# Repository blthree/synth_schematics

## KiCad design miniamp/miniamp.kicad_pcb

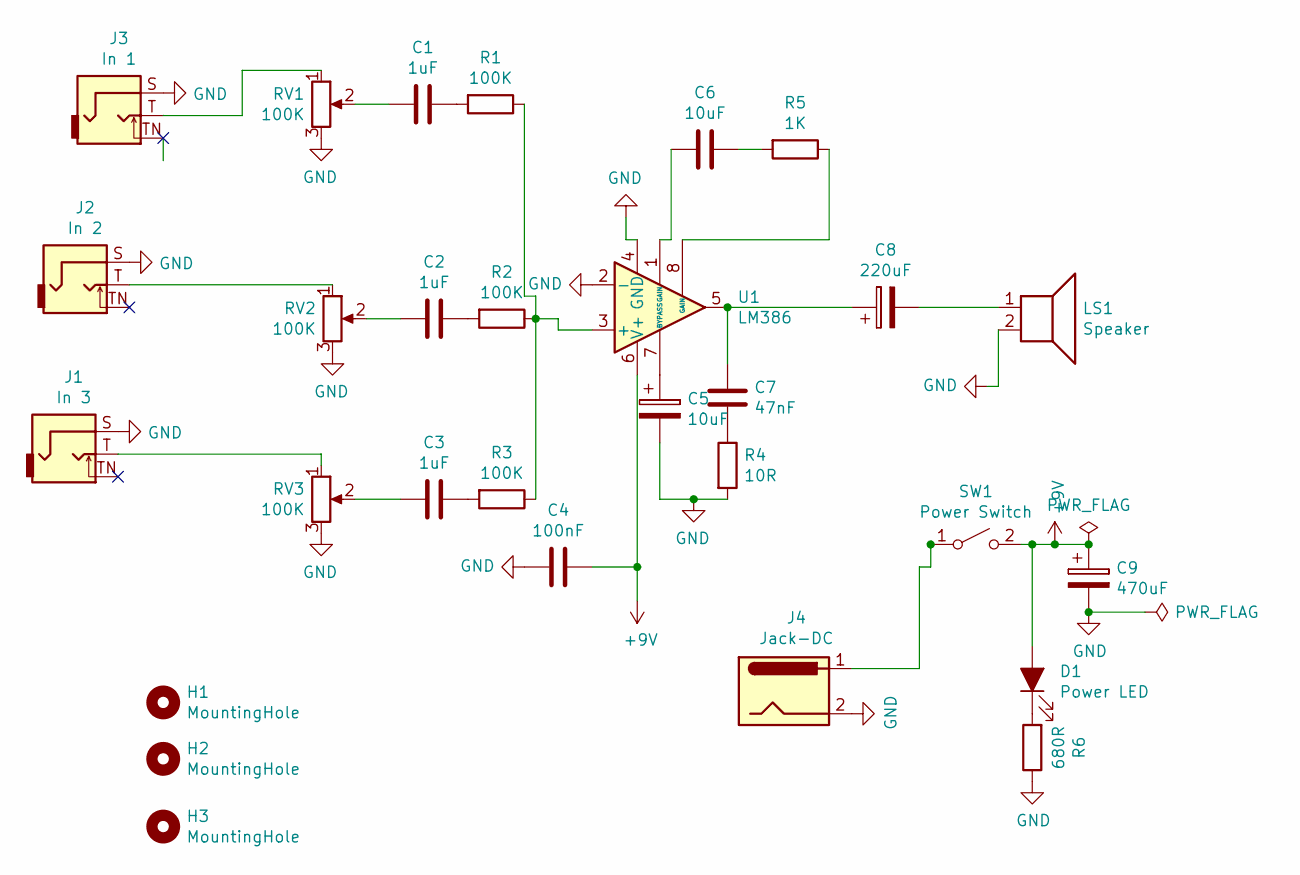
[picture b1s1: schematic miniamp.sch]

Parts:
C1, C2, C3: 1uF; C_Disc_D5.0mm_W2.5mm_P5.00mm
C4: 100nF; C_Disc_D5.0mm_W2.5mm_P5.00mm
C5: 10uF; CP_Radial_D5.0mm_P2.50mm
C6: 10uF; C_Disc_D5.0mm_W2.5mm_P5.00mm
C7: 47nF; C_Disc_D5.0mm_W2.5mm_P5.00mm
C8: 220uF; CP_Radial_D6.3mm_P2.50mm
C9: 470uF; CP_Radial_D6.3mm_P2.50mm
D1: Power LED; LED_D5.0mm
H1, H2, H3: MountingHole; MountingHole_3.2mm_M3_ISO7380
J1: In 3; CUI_SJ2-3592B-SMT-TR
J2: In 2; CUI_SJ2-3592B-SMT-TR
J3: In 1; CUI_SJ2-3592B-SMT-TR
J4: Jack-DC; BarrelJack_CUI_PJ-102AH_Horizontal
LS1: Speaker; JST_PH_B2B-PH-K_1x02_P2.00mm_Vertical
R1, R2, R3: 100K; R_Axial_DIN0207_L6.3mm_D2.5mm_P5.08mm_Vertical
R4: 10R; R_Axial_DIN0207_L6.3mm_D2.5mm_P5.08mm_Vertical
R5: 1K; R_Axial_DIN0207_L6.3mm_D2.5mm_P5.08mm_Vertical
R6: 680R; R_Axial_DIN0207_L6.3mm_D2.5mm_P5.08mm_Vertical
RV1, RV2, RV3: 100K; Potentiometer_Bourns_PTV09A-1_Single_Vertical
SW1: Power Switch; JST_PH_B2B-PH-K_1x02_P2.00mm_Vertical
U1: LM386; DIP-8_W7.62mm_Socket

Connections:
+9V: C4.1, C9.1, D1.2 (A), SW1.2 (B), U1.6 (V+)
GND: C4.2, C5.2, C9.2, J1.S, J2.S, J3.S, J4.2, LS1.2, R4.2, R6.1, RV1.3, RV2.3, RV3.3, U1.2 (-), U1.4 (GND)
unnamed: C1.1, R1.2
unnamed: C1.2, RV1.2
unnamed: C2.1, R2.2
unnamed: C2.2, RV2.2
unnamed: C3.1, R3.2
unnamed: C3.2, RV3.2
unnamed: C5.1, U1.7 (BYPASS)
unnamed: C6.1, R5.2
unnamed: C6.2, U1.1 (GAIN)
unnamed: C7.1, C8.1, U1.5
unnamed: C7.2, R4.1
unnamed: C8.2, LS1.1
unnamed: D1.1 (K), R6.2
unnamed: J1.T, RV3.1
unnamed: J2.T, RV2.1
unnamed: J3.T, RV1.1
unnamed: J4.1, SW1.1 (A)
unnamed: R1.1, R2.1, R3.1, U1.3 (+)
unnamed: R5.1, U1.8 (GAIN)

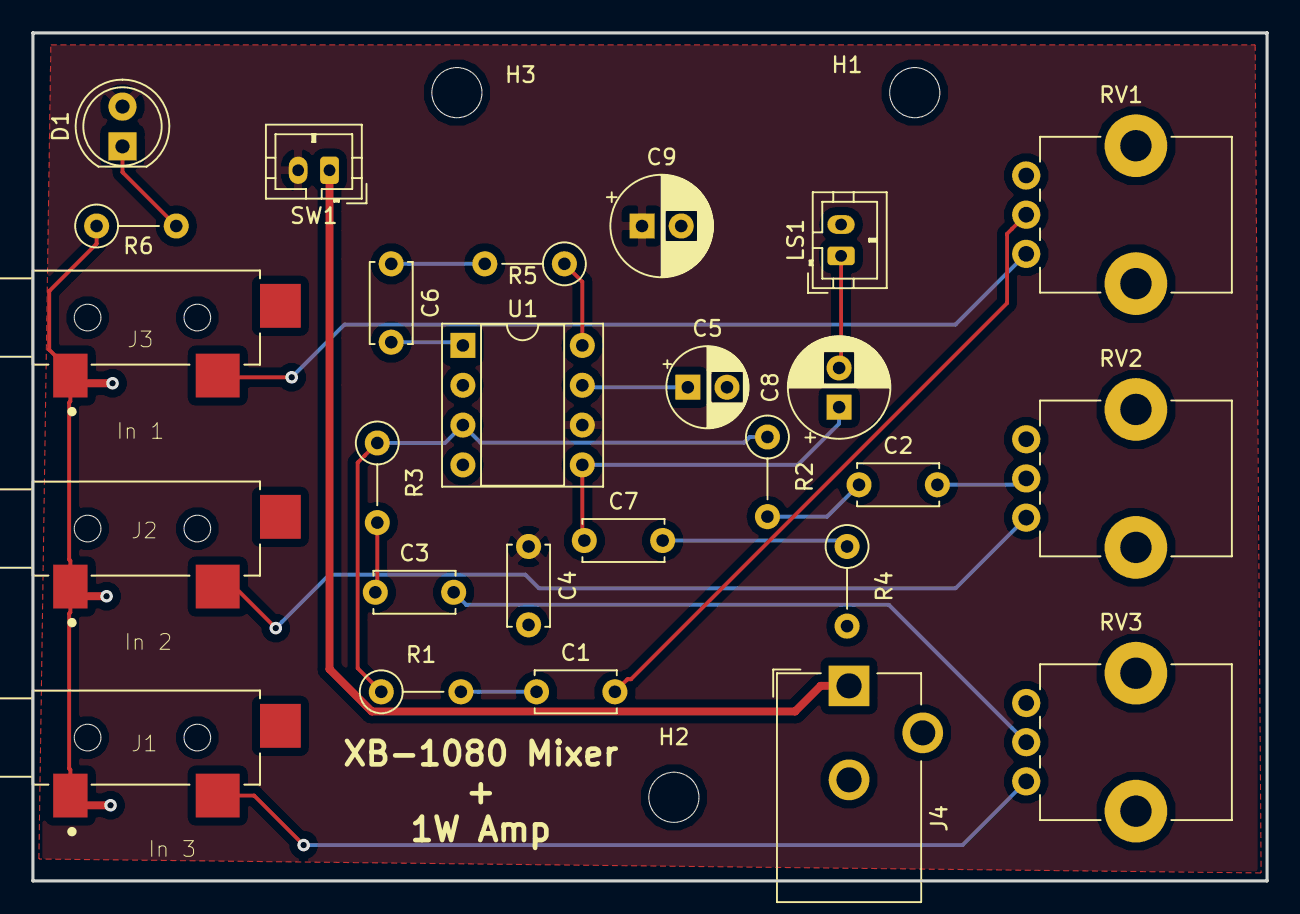
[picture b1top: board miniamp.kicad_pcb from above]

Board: 2 copper layers, 78.7 x 54.1 mm, 29 parts (0 on the bottom side), 21 nets.

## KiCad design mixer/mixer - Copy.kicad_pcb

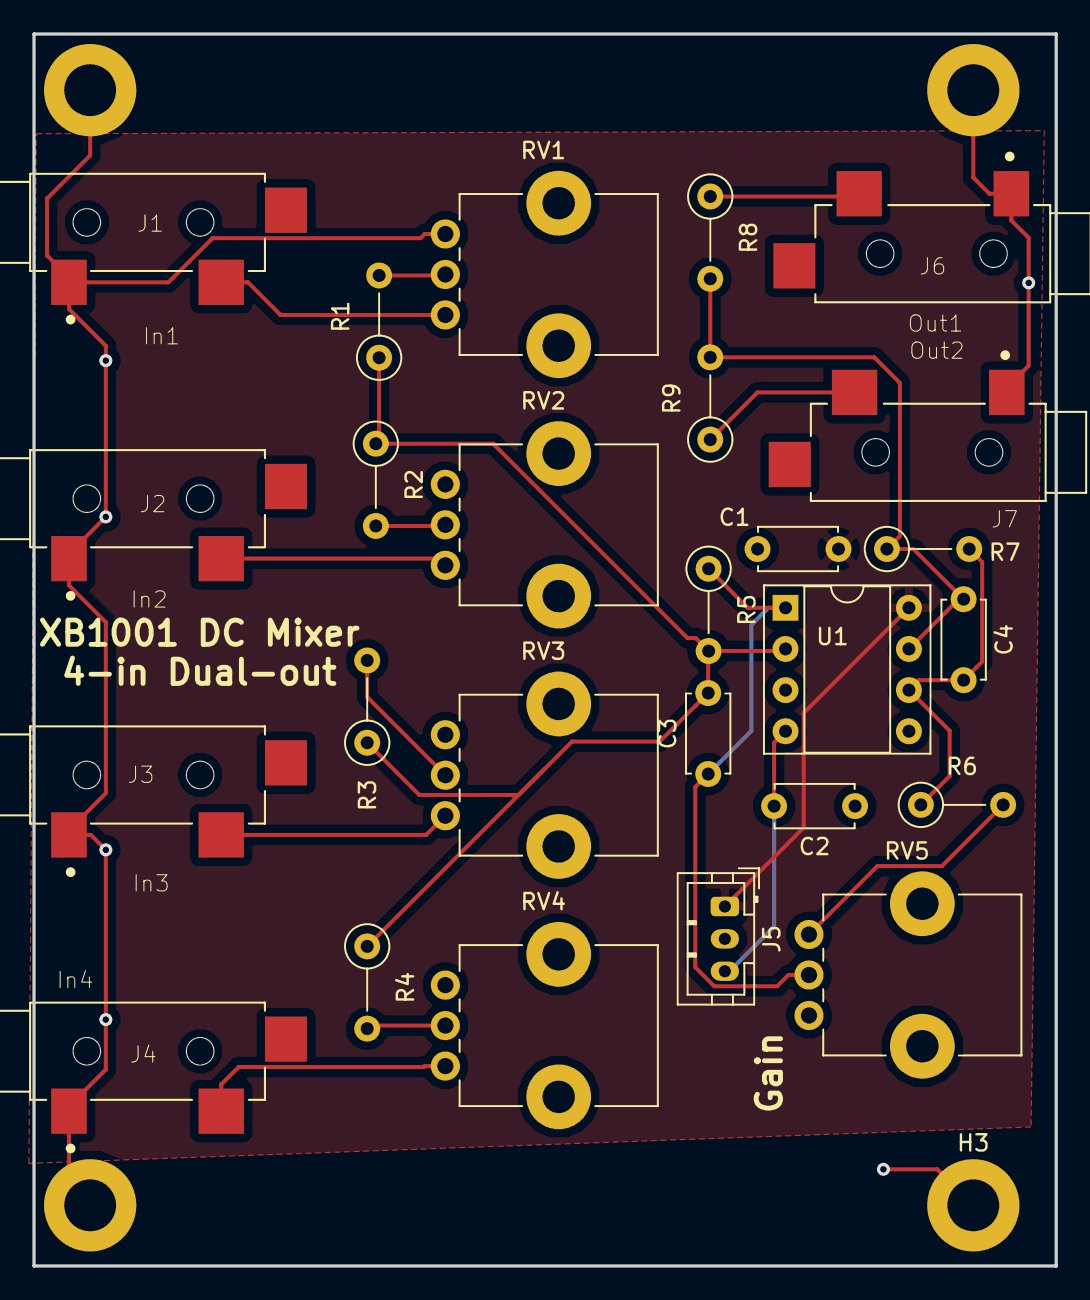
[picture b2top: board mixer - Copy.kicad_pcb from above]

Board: 2 copper layers, 63.1 x 76.1 mm, 30 parts (0 on the bottom side), 18 nets.

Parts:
C1, C2: 100nF; C_Disc_D4.7mm_W2.5mm_P5.00mm
C3, C4: 47pF; C_Disc_D4.7mm_W2.5mm_P5.00mm
H1, H2, H3, H4: MountingHole_Pad; MountingHole_3.2mm_M3_ISO7380_Pad
J1: In1; CUI_SJ2-3592B-SMT-TR
J2: In2; CUI_SJ2-3592B-SMT-TR
J3: In3; CUI_SJ2-3592B-SMT-TR
J4: In4; CUI_SJ2-3592B-SMT-TR
J5: Power; JST_PH_B3B-PH-K_1x03_P2.00mm_Vertical
J6: Out1; CUI_SJ2-3592B-SMT-TR
J7: Out2; CUI_SJ2-3592B-SMT-TR
R1, R2, R3, R4, R5, R7: 100K; R_Axial_DIN0207_L6.3mm_D2.5mm_P5.08mm_Vertical
R6: 10K; R_Axial_DIN0207_L6.3mm_D2.5mm_P5.08mm_Vertical
R8, R9: 1K; R_Axial_DIN0207_L6.3mm_D2.5mm_P5.08mm_Vertical
RV1, RV2, RV3, RV4, RV5: 104B; Potentiometer_Bourns_PTV09A-1_Single_Vertical
U1: TL072; DIP-8_W7.62mm_Socket

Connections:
+12V: C1.2, J5.1, U1.8
-12V: C2.2, J5.3, U1.4
GND: C1.1, C2.1, H1.1, H2.1, H3.1, H4.1, J1.S, J2.S, J3.S, J4.S, J5.2, J6.S, J7.S, RV1.3, RV2.3, RV3.3, RV4.3, U1.3, U1.5
unnamed: C3.1, R5.1, RV5.2, U1.1
unnamed: C3.2, R1.1, R2.1, R3.1, R4.1, R5.2, U1.2
unnamed: C4.1, R7.1, R8.2, R9.2, U1.7
unnamed: C4.2, R6.1, R7.2, U1.6
unnamed: J1.T, RV1.1
unnamed: J2.T, RV2.1
unnamed: J3.T, RV3.1
unnamed: J4.T, RV4.1
unnamed: J6.T, R8.1
unnamed: J7.T, R9.1
unnamed: R1.2, RV1.2
unnamed: R2.2, RV2.2
unnamed: R3.2, RV3.2
unnamed: R4.2, RV4.2
unnamed: R6.2, RV5.3

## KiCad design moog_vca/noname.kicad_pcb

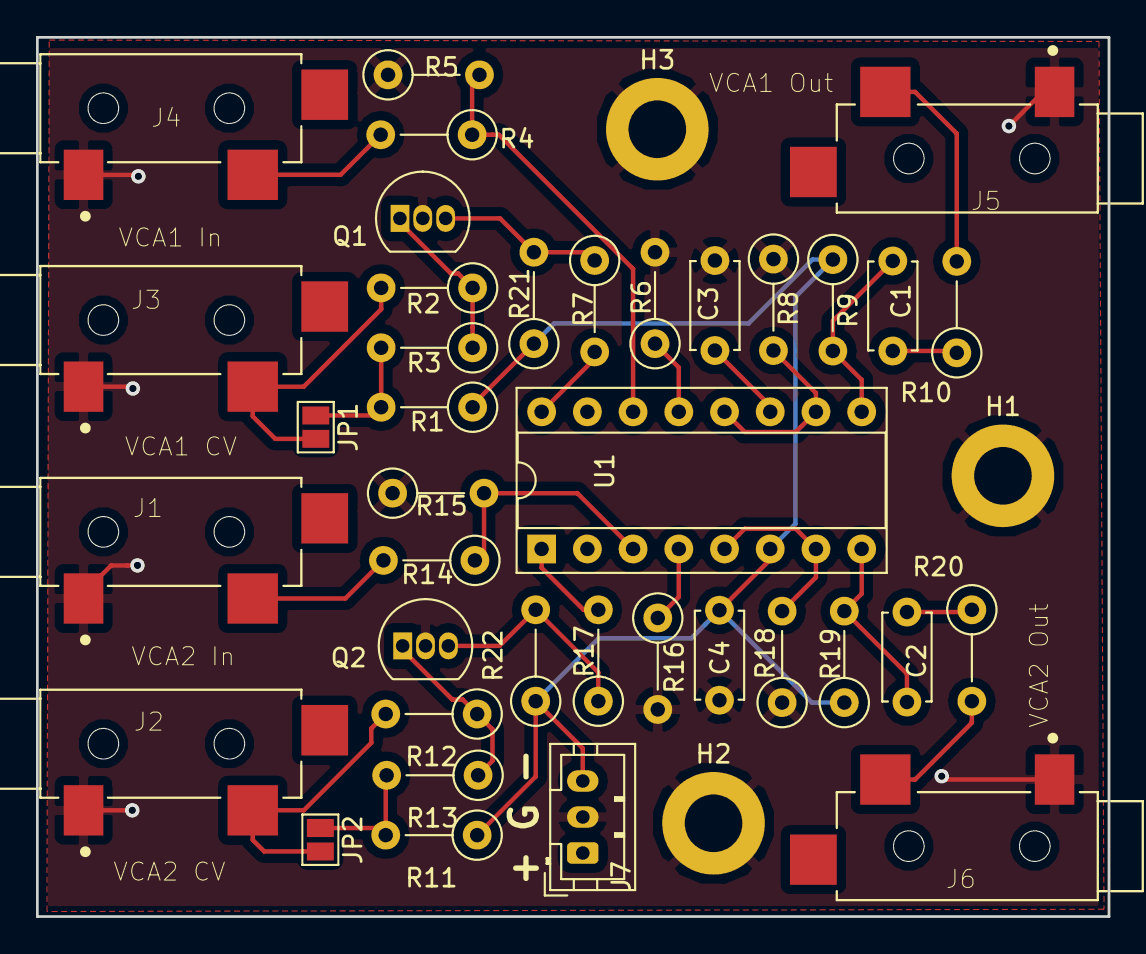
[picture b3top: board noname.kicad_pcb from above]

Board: 2 copper layers, 59.5 x 48.8 mm, 41 parts (0 on the bottom side), 27 nets.

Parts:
C1, C2: 2.2uF; C_Disc_D4.7mm_W2.5mm_P5.00mm
C3, C4: 0.10uF; C_Disc_D4.7mm_W2.5mm_P5.00mm
H1, H2, H3: MountingHole_Pad; MountingHole_3.2mm_M3_ISO7380_Pad
J1: VCA2 In; CUI_SJ2-3592B-SMT-TR
J2: VCA2 CV; CUI_SJ2-3592B-SMT-TR
J3: VCA1 CV; CUI_SJ2-3592B-SMT-TR
J4: VCA1 In; CUI_SJ2-3592B-SMT-TR
J5: VCA1 Out; CUI_SJ2-3592B-SMT-TR
J6: VCA2 Out; CUI_SJ2-3592B-SMT-TR
J7: Power; JST_PH_B3B-PH-K_1x03_P2.00mm_Vertical
JP1, JP2: Jumper_NO_Small; SolderJumper-2_P1.3mm_Open_Pad1.0x1.5mm
Q1, Q2: 2N3906; TO-92_Inline
R1, R11: 499k; R_Axial_DIN0207_L6.3mm_D2.5mm_P5.08mm_Vertical
R2, R3, R7, R12, R13, R17: 10k; R_Axial_DIN0207_L6.3mm_D2.5mm_P5.08mm_Vertical
R4, R14: 33.2k; R_Axial_DIN0207_L6.3mm_D2.5mm_P5.08mm_Vertical
R5, R6, R15, R16: 681R; R_Axial_DIN0207_L6.3mm_D2.5mm_P5.08mm_Vertical
R8, R18: 4.99k; R_Axial_DIN0207_L6.3mm_D2.5mm_P5.08mm_Vertical
R9, R19: 12,1k; R_Axial_DIN0207_L6.3mm_D2.5mm_P5.08mm_Vertical
R10, R20: 475R; R_Axial_DIN0207_L6.3mm_D2.5mm_P5.08mm_Vertical
R21, R22: 4.75M; R_Axial_DIN0207_L6.3mm_D2.5mm_P5.08mm_Vertical
U1: LM13700; DIP-16_W7.62mm_Socket

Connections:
+9V: C3.1, J7.1, U1.11
-9V: C4.1, J7.3, R1.1, R9.1, R11.1, R19.1, R21.1, R22.1, U1.6
GND: C3.2, C4.2, H1.1, H2.1, H3.1, J1.S, J2.S, J3.S, J4.S, J5.S, J6.S, J7.2, Q1.2, Q2.2, R5.1, R6.2, R8.1, R15.1, R16.2, R18.1
unnamed: C1.1, R10.1
unnamed: C1.2, R9.2, U1.9
unnamed: C2.1, R20.1
unnamed: C2.2, R19.2, U1.8
unnamed: Q1.1, R2.1, R3.1
unnamed: Q1.3, R7.1, R21.2
unnamed: Q2.1, R12.1, R13.1
unnamed: Q2.3, R17.1, R22.2
unnamed: R4.1, R5.2, U1.14
unnamed: R6.1, U1.13
unnamed: R7.2, U1.16
unnamed: R8.2, U1.10, U1.12
unnamed: R14.1, R15.2, U1.3
unnamed: R16.1, U1.4
unnamed: R17.2, U1.1
unnamed: R18.2, U1.5, U1.7
VCA1_CV1: J3.T, JP1.2, R2.2
VCA1_CV2: JP1.1, R1.2, R3.2
VCA1_In: J4.T, R4.2
VCA1_Out: J5.T, R10.2
VCA2_CV1: J2.T, JP2.2, R12.2
VCA2_CV2: JP2.1, R11.2, R13.2
VCA2_In: J1.T, R14.2
VCA2_Out: J6.T, R20.2

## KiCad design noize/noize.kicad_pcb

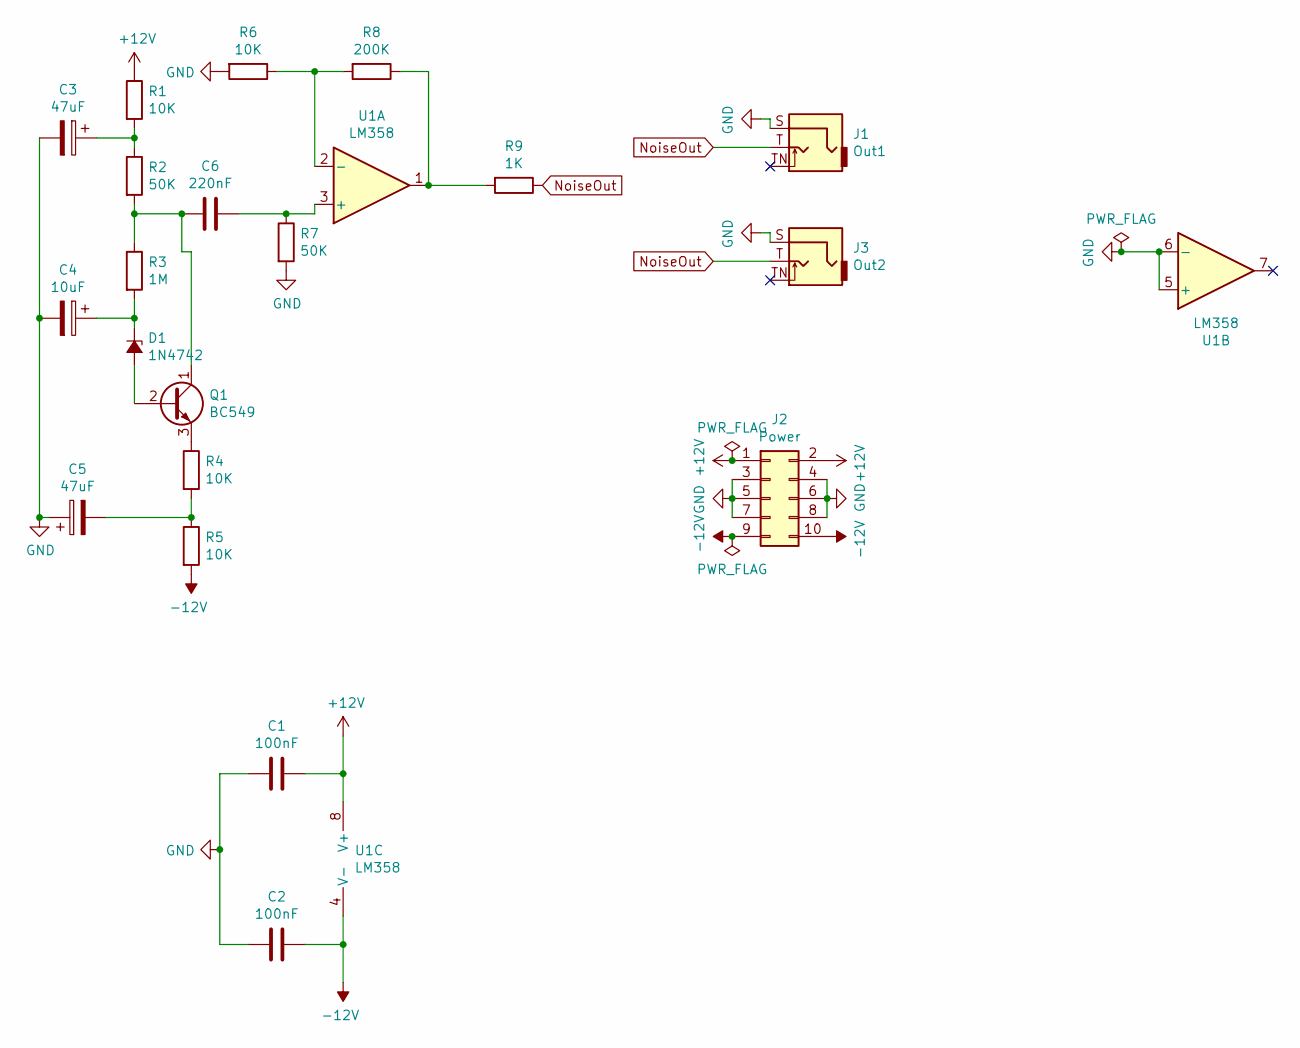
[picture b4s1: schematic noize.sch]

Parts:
C1, C2: 100nF; C_Disc_D4.7mm_W2.5mm_P5.00mm
C3, C5: 47uF; CP_Radial_D5.0mm_P2.50mm
C4: 10uF; CP_Radial_D5.0mm_P2.50mm
C6: 220nF; CP_Radial_D5.0mm_P2.50mm
D1: 1N4742; D_DO-35_SOD27_P7.62mm_Horizontal
J1: Out1; Jack_3.5mm_QingPu_WQP-PJ398SM_Vertical_CircularHoles
J2: Power; PinHeader_2x05_P2.54mm_Vertical
J3: Out2; Jack_3.5mm_QingPu_WQP-PJ398SM_Vertical_CircularHoles
Q1: BC549; TO-92_Inline
R1, R4, R5, R6: 10K; R_Axial_DIN0207_L6.3mm_D2.5mm_P5.08mm_Vertical
R2, R7: 50K; R_Axial_DIN0207_L6.3mm_D2.5mm_P5.08mm_Vertical
R3: 1M; R_Axial_DIN0207_L6.3mm_D2.5mm_P5.08mm_Vertical
R8: 200K; R_Axial_DIN0207_L6.3mm_D2.5mm_P5.08mm_Vertical
R9: 1K; R_Axial_DIN0207_L6.3mm_D2.5mm_P5.08mm_Vertical
U1: LM358; DIP-8_W7.62mm_Socket

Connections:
+12V: C1.2, J2.1, J2.2, R1.1, U1.8 (V+)
-12V: C2.2, J2.9, J2.10, R5.2, U1.4 (V-)
GND: C1.1, C2.1, C3.2, C4.2, C5.1, J1.S, J2.3, J2.4, J2.5, J2.6, J2.7, J2.8, J3.S, R6.2, R7.2, U1.5 (+), U1.6 (-)
unnamed: C3.1, R1.2, R2.1
unnamed: C4.1, D1.1 (K), R3.2
unnamed: C5.2, R4.2, R5.1
unnamed: C6.1, Q1.1 (C), R2.2, R3.1
unnamed: C6.2, R7.1, U1.3 (+)
unnamed: D1.2 (A), Q1.2 (B)
unnamed: Q1.3 (E), R4.1
unnamed: R6.1, R8.2, U1.2 (-)
unnamed: R8.1, R9.2, U1.1
NoiseOut: J1.T, J3.T, R9.1

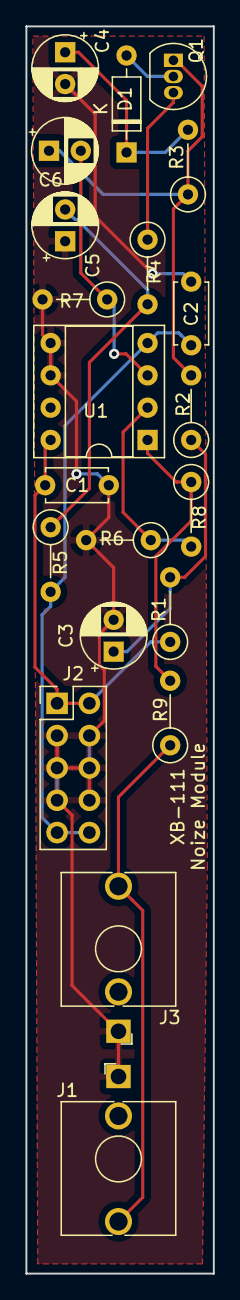
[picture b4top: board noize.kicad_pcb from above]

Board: 2 copper layers, 14.7 x 98.0 mm, 21 parts (0 on the bottom side), 13 nets.

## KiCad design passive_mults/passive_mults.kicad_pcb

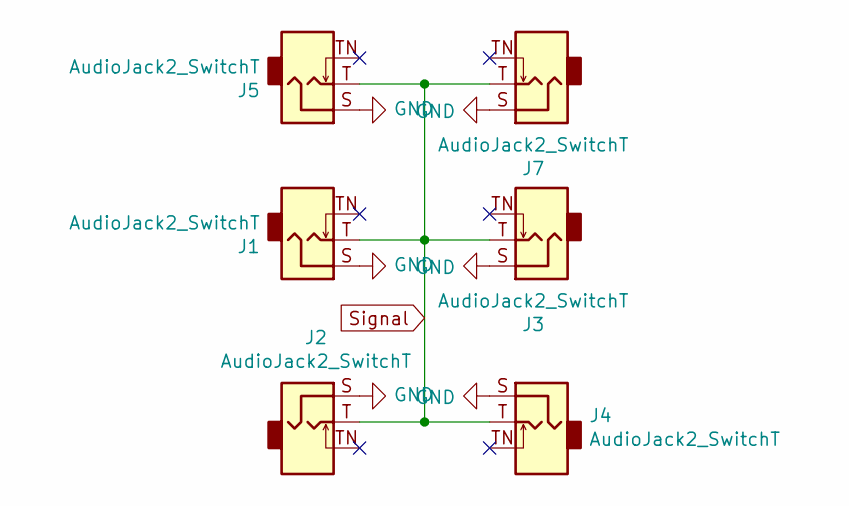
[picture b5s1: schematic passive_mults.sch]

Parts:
J1, J2, J3, J4, J5, J7: AudioJack2_SwitchT; Jack_3.5mm_QingPu_WQP-PJ398SM_Vertical_CircularHoles

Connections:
GND: J1.S, J2.S, J3.S, J4.S, J5.S, J7.S
unnamed: J1.T, J2.T, J3.T, J4.T, J5.T, J7.T

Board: 2 copper layers, 6 parts (0 on the bottom side), 2 nets, no tracks yet.

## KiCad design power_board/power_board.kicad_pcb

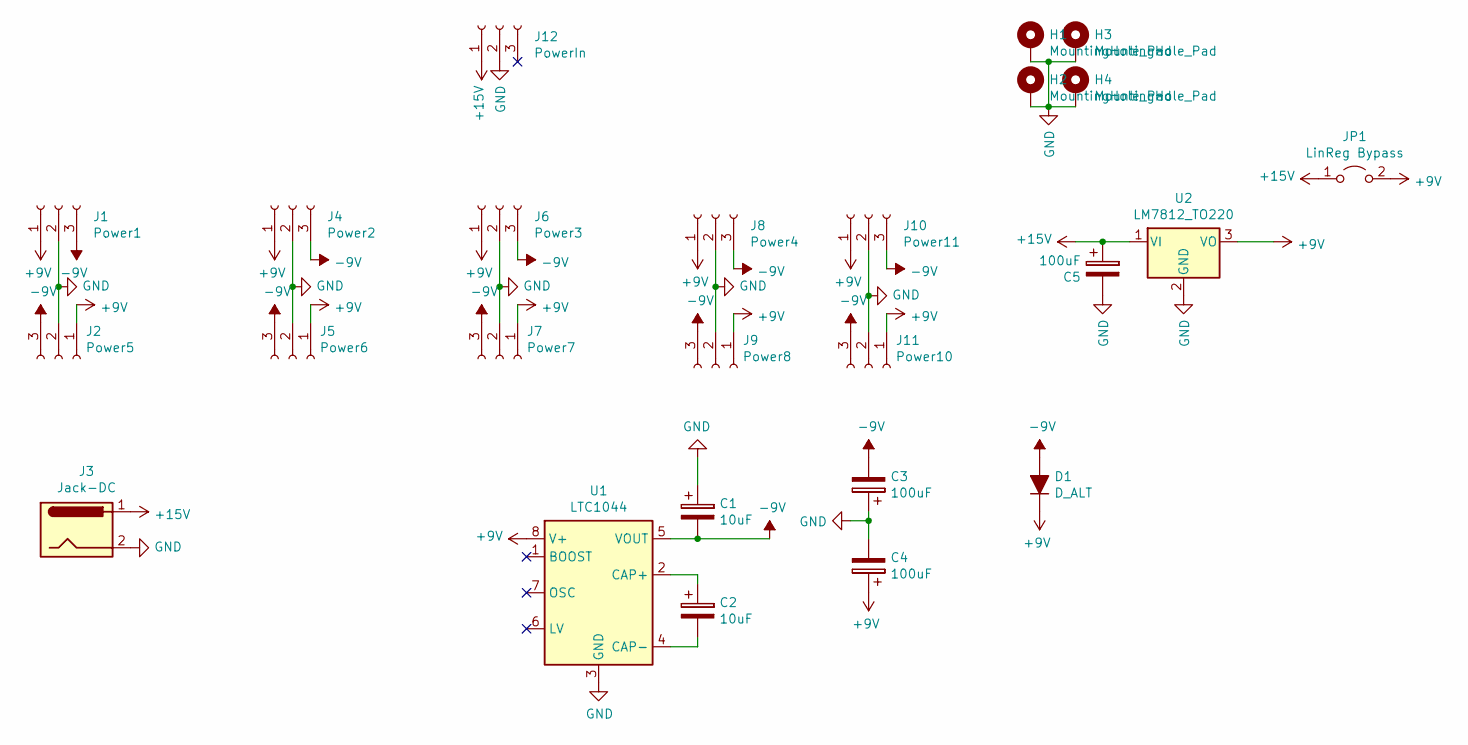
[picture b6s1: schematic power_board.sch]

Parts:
C1, C2: 10uF; CP_Radial_D7.5mm_P2.50mm
C3, C4, C5: 100uF; CP_Radial_D7.5mm_P2.50mm
D1: D_ALT; D_DO-41_SOD81_P7.62mm_Horizontal
H1, H2, H3, H4: MountingHole_Pad; MountingHole_3.2mm_M3_ISO14580_Pad
J1: Power1; PinHeader_1x03_P2.54mm_Vertical
J2: Power5; PinHeader_1x03_P2.54mm_Vertical
J3: Jack-DC; BarrelJack_CUI_PJ-102AH_Horizontal
J4: Power2; PinHeader_1x03_P2.54mm_Vertical
J5: Power6; JST_PH_B3B-PH-K_1x03_P2.00mm_Vertical
J6: Power3; PinHeader_1x03_P2.54mm_Vertical
J7: Power7; JST_PH_B3B-PH-K_1x03_P2.00mm_Vertical
J8: Power4; PinHeader_1x03_P2.54mm_Vertical
J9: Power8; JST_PH_B3B-PH-K_1x03_P2.00mm_Vertical
J10: Power11; JST_PH_B3B-PH-K_1x03_P2.00mm_Vertical
J11: Power10; JST_PH_B3B-PH-K_1x03_P2.00mm_Vertical
J12: PowerIn; PinHeader_1x03_P2.54mm_Vertical
JP1: LinReg Bypass; SolderJumper-2_P1.3mm_Open_Pad1.0x1.5mm
U1: LTC1044; DIP-8_W7.62mm_Socket
U2: LM7812_TO220; TO-220-3_Horizontal_TabDown

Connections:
+9V: C4.1, D1.1 (K), J1.1, J2.1, J4.1, J5.1, J6.1, J7.1, J8.1, J9.1, J10.1, J11.1, JP1.2 (B), U1.8 (V+), U2.3 (VO)
+15V: C5.1, J3.1, J12.1, JP1.1 (A), U2.1 (VI)
-9V: C1.2, C3.2, D1.2 (A), J1.3, J2.3, J4.3, J5.3, J6.3, J7.3, J8.3, J9.3, J10.3, J11.3, U1.5 (VOUT)
GND: C1.1, C3.1, C4.2, C5.2, H1.1, H2.1, H3.1, H4.1, J1.2, J2.2, J3.2, J4.2, J5.2, J6.2, J7.2, J8.2, J9.2, J10.2, J11.2, J12.2, U1.3 (GND), U2.2 (GND)
unnamed: C2.1, U1.2 (CAP+)
unnamed: C2.2, U1.4 (CAP-)

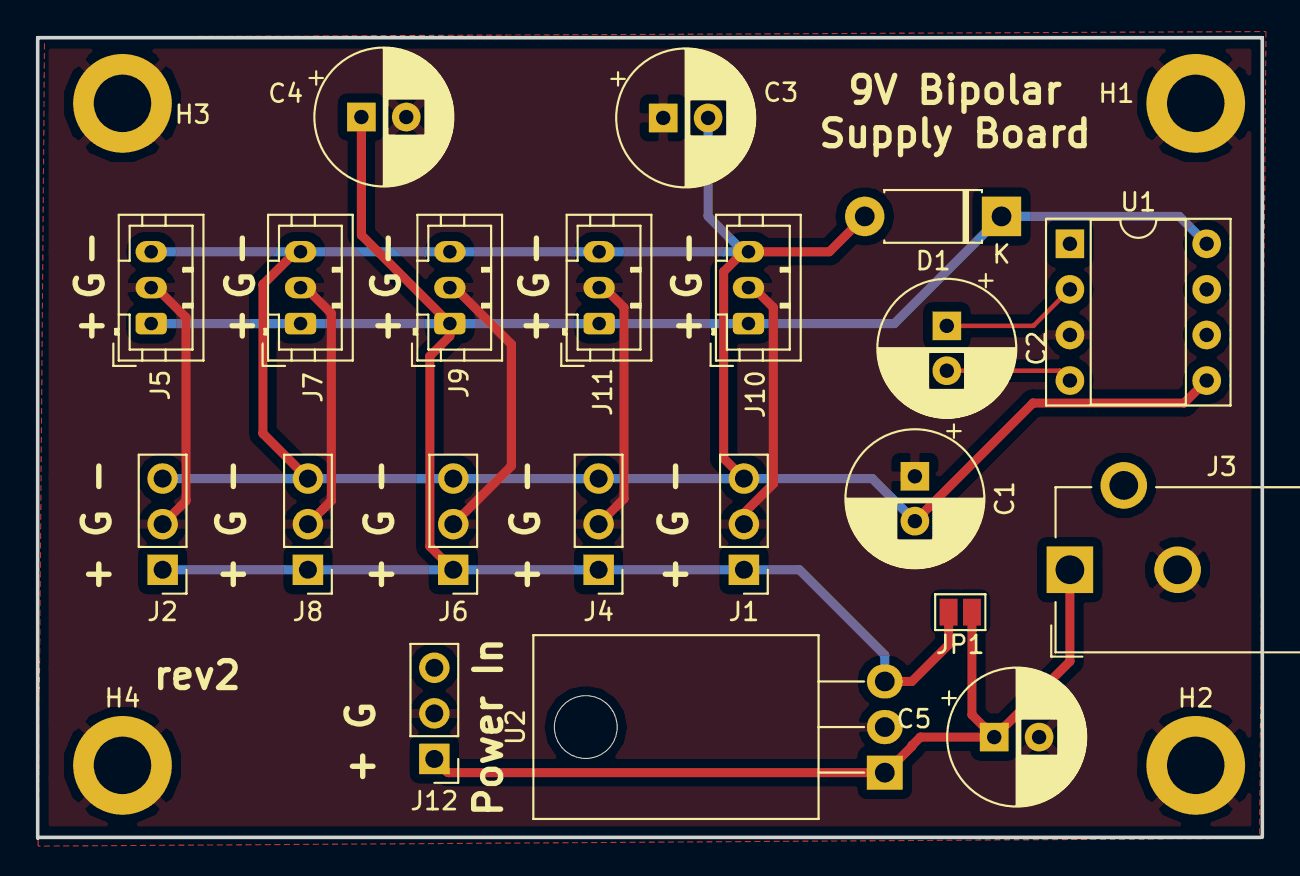
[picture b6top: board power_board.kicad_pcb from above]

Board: 2 copper layers, 68.2 x 44.6 mm, 25 parts (0 on the bottom side), 6 nets.
